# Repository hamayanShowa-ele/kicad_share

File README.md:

# kicad_share
kicad share data.

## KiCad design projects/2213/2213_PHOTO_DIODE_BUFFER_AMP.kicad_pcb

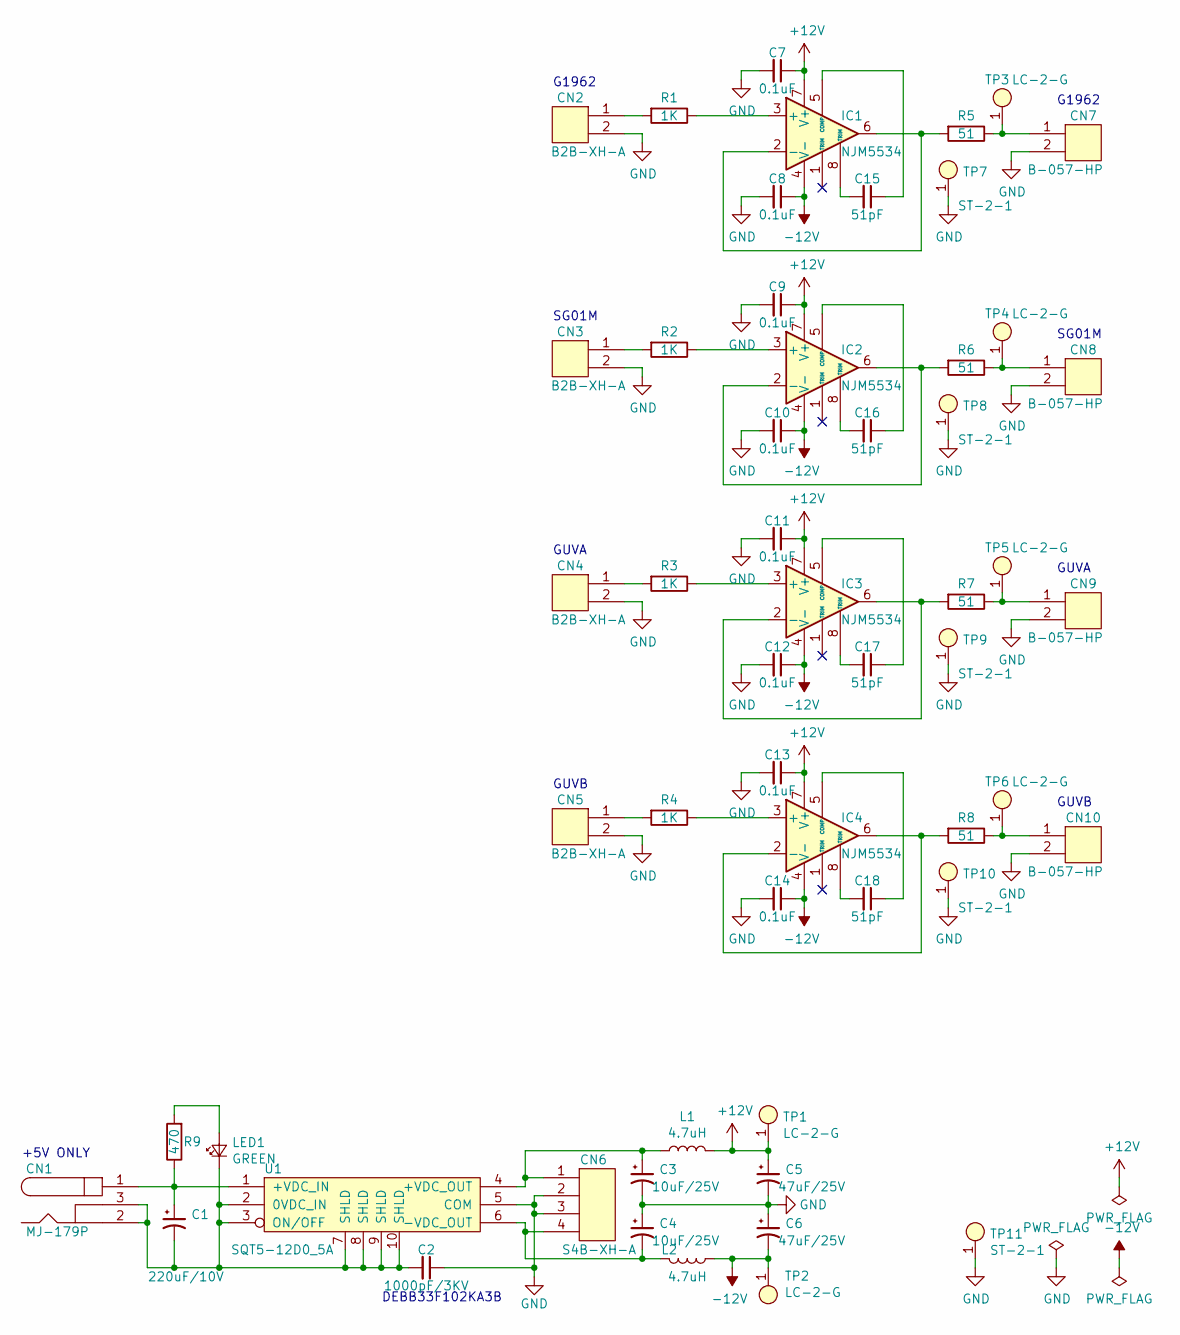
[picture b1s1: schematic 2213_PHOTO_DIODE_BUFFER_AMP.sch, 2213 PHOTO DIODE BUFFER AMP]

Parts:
C1: 220uF/10V; CP_Radial_D8.00mm_P2.50mm
C2: 1000pF/3KV; C_DEBB33F102KA
C3, C4: 10uF/25V; CP_D6R3_P2R5
C5, C6: 47uF/25V; CP_D6R3_P2R5
C7, C8, C9, C10, C11, C12, C13, C14: 0.1uF; C_TH_5R08
C15, C16, C17, C18: 51pF; C_TH_5R08
CN1: MJ-179P; cn_MJ-179P
CN2, CN3, CN4, CN5: B2B-XH-A; cn_B2B-XH-A
CN6: S4B-XH-A; cn_S4B-XH-A
CN7, CN8, CN9, CN10: B-057-HP; cn_BNC_B-057-HP
IC1, IC2, IC3, IC4: NJM5534; ic_DIP-8_W7.62mm
L1, L2: 4.7uH; l_LAL04SK4R7K
LED1: GREEN; LED_D3.0mm_center
R1, R2, R3, R4: 1K; R_TH_5R08
R5, R6, R7, R8: 51; R_TH_5R08
R9: 470; R_TH_5R08
TP1, TP2, TP3, TP4, TP5, TP6: LC-2-G; tp_LC-2-G
TP7, TP8, TP9, TP10, TP11: ST-2-1; tp_LC-2-G
U1: SQT5-12D0_5A; u_SQT5-24S05

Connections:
+12V: C5.1, C7.1, C9.1, C11.1, C13.1, IC1.7 (V+), IC2.7 (V+), IC3.7 (V+), IC4.7 (V+), L1.2, TP1.1
-12V: C6.2, C8.1, C10.1, C12.1, C14.1, IC1.4 (V-), IC2.4 (V-), IC3.4 (V-), IC4.4 (V-), L2.1, TP2.1
GND: C2.1, C3.2, C4.1, C5.2, C6.1, C7.2, C8.2, C9.2, C10.2, C11.2, C12.2, C13.2, C14.2, CN2.2, CN3.2, CN4.2, CN5.2, CN6.2, CN6.3, CN7.2, CN8.2, CN9.2, CN10.2, TP7.1, TP8.1, TP9.1, TP10.1, TP11.1, U1.5 (COM)
unnamed: C1.1, CN1.1, R9.1, U1.1 (+VDC_IN)
unnamed: C1.2, C2.2, CN1.2, CN1.3, LED1.2 (K), U1.2 (0VDC_IN), U1.3 (ON/OFF), U1.7 (SHLD), U1.8 (SHLD), U1.9 (SHLD), U1.10 (SHLD)
unnamed: C3.1, CN6.1, L1.1, U1.4 (+VDC_OUT)
unnamed: C4.2, CN6.4, L2.2, U1.6 (-VDC_OUT)
unnamed: C15.1, IC1.5 (COMP)
unnamed: C15.2, IC1.8 (TRIM)
unnamed: C16.1, IC2.5 (COMP)
unnamed: C16.2, IC2.8 (TRIM)
unnamed: C17.1, IC3.5 (COMP)
unnamed: C17.2, IC3.8 (TRIM)
unnamed: C18.1, IC4.5 (COMP)
unnamed: C18.2, IC4.8 (TRIM)
unnamed: CN2.1, R1.2
unnamed: CN3.1, R2.2
unnamed: CN4.1, R3.2
unnamed: CN5.1, R4.2
unnamed: CN7.1, R5.1, TP3.1
unnamed: CN8.1, R6.1, TP4.1
unnamed: CN9.1, R7.1, TP5.1
unnamed: CN10.1, R8.1, TP6.1
unnamed: IC1.2 (-), IC1.6, R5.2
unnamed: IC1.3 (+), R1.1
unnamed: IC2.2 (-), IC2.6, R6.2
unnamed: IC2.3 (+), R2.1
unnamed: IC3.2 (-), IC3.6, R7.2
unnamed: IC3.3 (+), R3.1
unnamed: IC4.2 (-), IC4.6, R8.2
unnamed: IC4.3 (+), R4.1
unnamed: LED1.1 (A), R9.2

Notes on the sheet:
+5V ONLY
G1962
SG01M
GUVA
GUVB
DEBB33F102KA3B

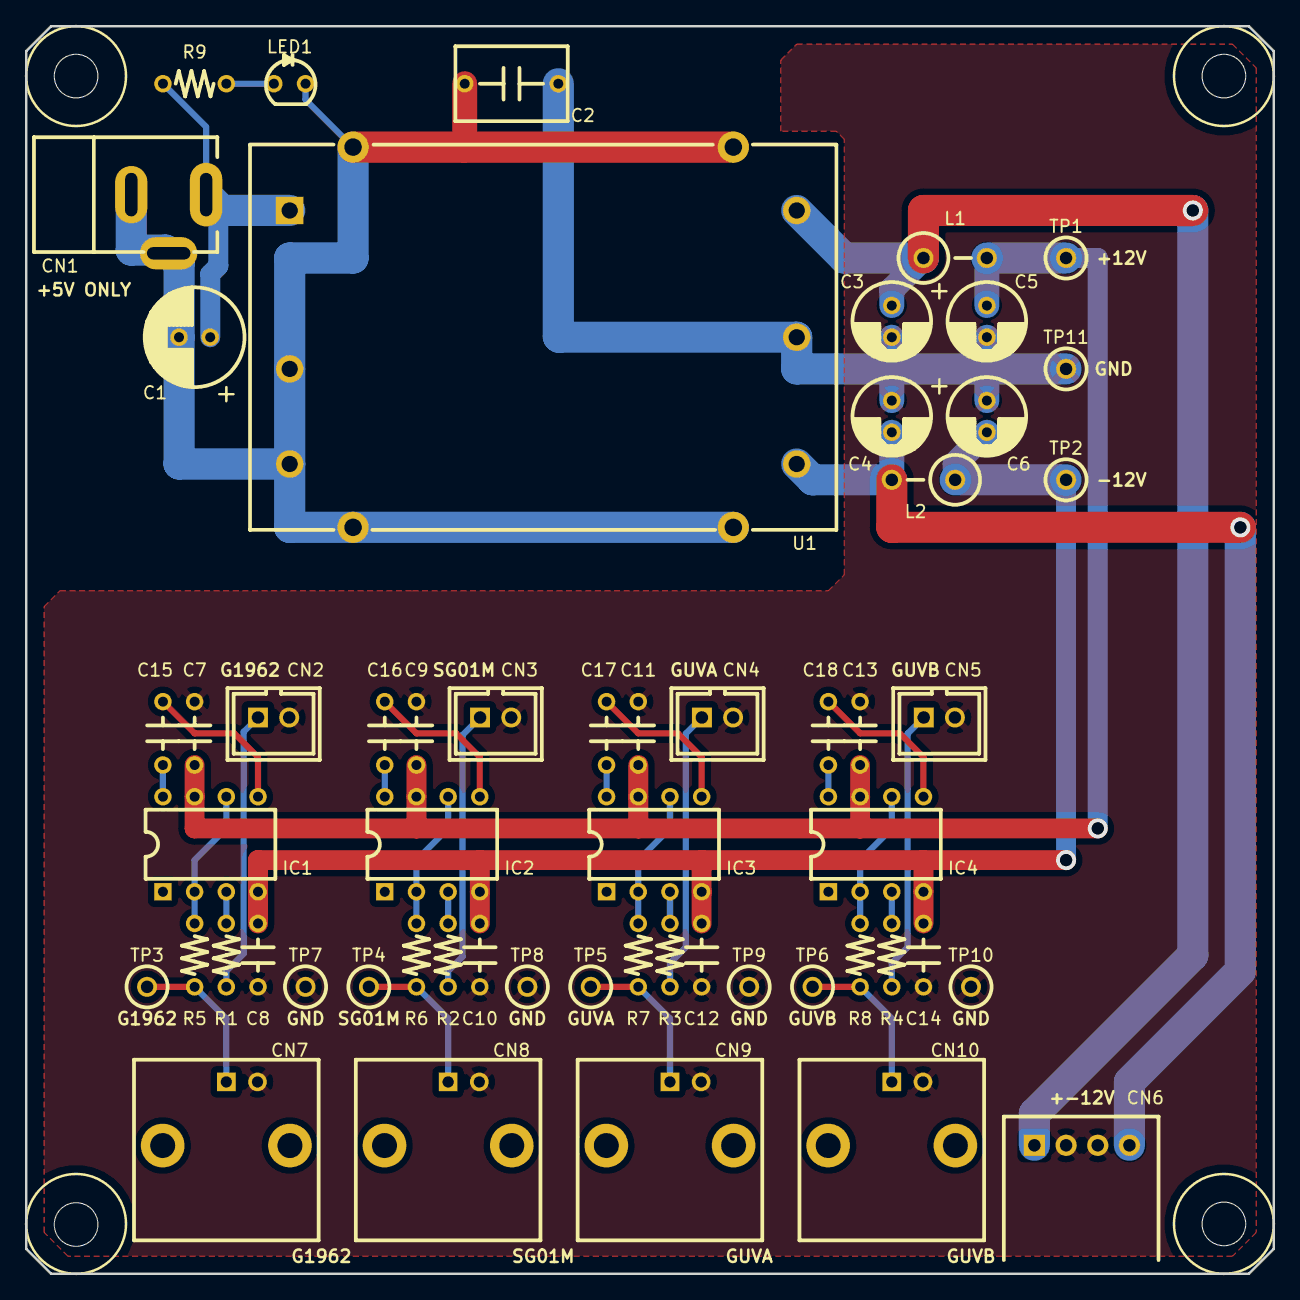
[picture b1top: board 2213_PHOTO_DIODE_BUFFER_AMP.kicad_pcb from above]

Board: 2 copper layers, 100.0 x 100.0 mm, 56 parts (0 on the bottom side), 32 nets.

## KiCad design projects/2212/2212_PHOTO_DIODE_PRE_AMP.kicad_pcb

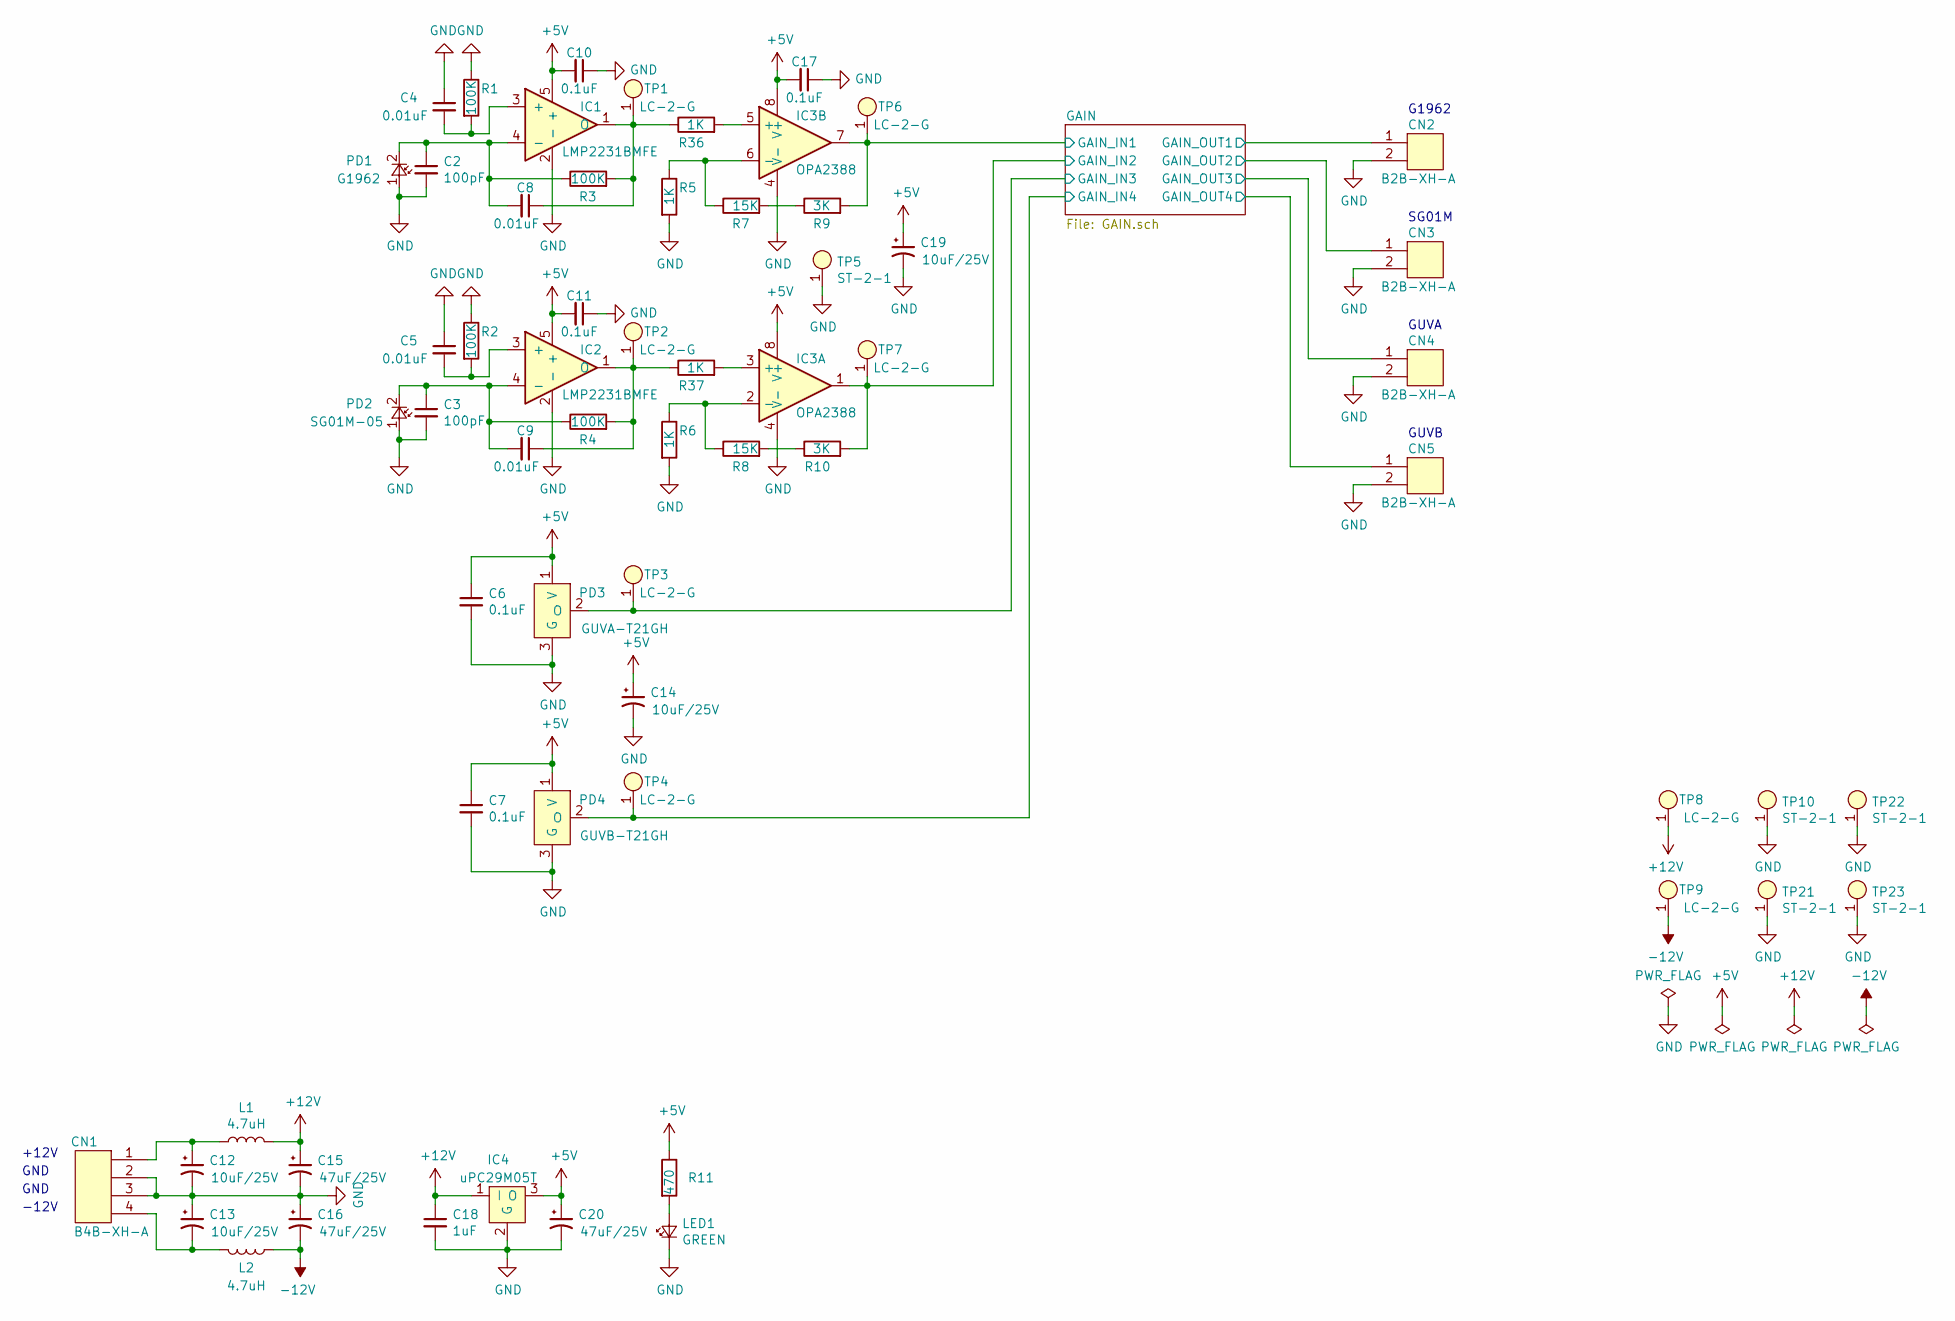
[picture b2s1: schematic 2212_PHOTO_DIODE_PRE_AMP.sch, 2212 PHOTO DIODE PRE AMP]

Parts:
C2, C3: 100pF; C_0603
C4, C5, C8, C9: 0.01uF; C_0603
C6, C7, C10, C11, C17: 0.1uF; C_0603
C12, C13, C14, C19: 10uF/25V; CP_Radial_D6.50mm_P2.50mm
C15, C16, C20: 47uF/25V; CP_Radial_D6.50mm_P2.50mm
C18: 1uF; C_0603
CN1: B4B-XH-A; cn_B4B-XH-A
CN2, CN3, CN4, CN5: B2B-XH-A; cn_B2B-XH-A
IC1, IC2: LMP2231BMFE; ic_SOT-23-5
IC3: OPA2388; SOIC-8
IC4: uPC29M05T; TO-252-2
L1, L2: 4.7uH; l_LAL04SK4R7K
LED1: GREEN; LED_D3.0mm_center
PD1: G1962; pd_G1962
PD2: SG01M-05; pd_SG01M
PD3: GUVA-T21GH; pd_GUVB-T21GH
PD4: GUVB-T21GH; pd_GUVB-T21GH
R1, R2, R3, R4: 100K; C_0805
R5, R6, R36, R37: 1K; C_0805
R7, R8: 15K; C_0805
R9, R10: 3K; C_0805
R11: 470; C_0603
TP1, TP2, TP3, TP4, TP6, TP7, TP8, TP9: LC-2-G; tp_LC-2-G
TP5, TP10, TP21, TP22, TP23: ST-2-1; tp_LC-2-G

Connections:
+5V: C6.1, C7.1, C10.2, C11.2, C14.1, C17.2, C19.1, C20.1, IC1.5 (+), IC2.5 (+), IC3.8 (V+), IC4.3 (O), PD3.1 (V), PD4.1 (V), R11.1
+12V: C15.1, C18.1, IC4.1 (I), L1.2, TP8.1; also elsewhere on the board
-12V: C16.2, L2.1, TP9.1; also elsewhere on the board
/GAIN/GAIN_IN1: IC3.7, R9.2, TP6.1; also elsewhere on the board
/GAIN/GAIN_IN2: IC3.1, R10.2, TP7.1; also elsewhere on the board
/GAIN/GAIN_IN3: PD3.2 (O), TP3.1; also elsewhere on the board
/GAIN/GAIN_IN4: PD4.2 (O), TP4.1; also elsewhere on the board
/GAIN/GAIN_OUT1: CN2.1; also elsewhere on the board
/GAIN/GAIN_OUT2: CN3.1; also elsewhere on the board
/GAIN/GAIN_OUT3: CN4.1; also elsewhere on the board
/GAIN/GAIN_OUT4: CN5.1; also elsewhere on the board
GND: C2.2, C3.2, C4.1, C5.1, C6.2, C7.2, C10.1, C11.1, C12.2, C13.1, C14.2, C15.2, C16.1, C17.1, C18.2, C19.2, C20.2, CN1.2, CN1.3, CN2.2, CN3.2, CN4.2, CN5.2, IC1.2 (-), IC2.2 (-), IC3.4 (V-), IC4.2 (G), LED1.2 (K), PD1.1, PD2.1, PD3.3 (G), PD4.3 (G), R1.1, R2.1, R5.2, R6.2, TP5.1, TP10.1, TP21.1, TP22.1, TP23.1; also elsewhere on the board
unnamed: C2.1, C8.2, IC1.4 (-), PD1.2, R3.1
unnamed: C3.1, C9.2, IC2.4 (-), PD2.2, R4.1
unnamed: C4.2, IC1.3 (+), R1.2
unnamed: C5.2, IC2.3 (+), R2.2
unnamed: C8.1, IC1.1 (O), R3.2, R36.1, TP1.1
unnamed: C9.1, IC2.1 (O), R4.2, R37.1, TP2.1
unnamed: C12.1, CN1.1, L1.1
unnamed: C13.2, CN1.4, L2.2
unnamed: IC3.2 (-), R6.1, R8.1
unnamed: IC3.3 (+), R37.2
unnamed: IC3.5 (+), R36.2
unnamed: IC3.6 (-), R5.1, R7.1
unnamed: LED1.1 (A), R11.2
unnamed: R7.2, R9.1
unnamed: R8.2, R10.1

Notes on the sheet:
+12V
G1962
SG01M
GUVA
GUVB
-12V
GND

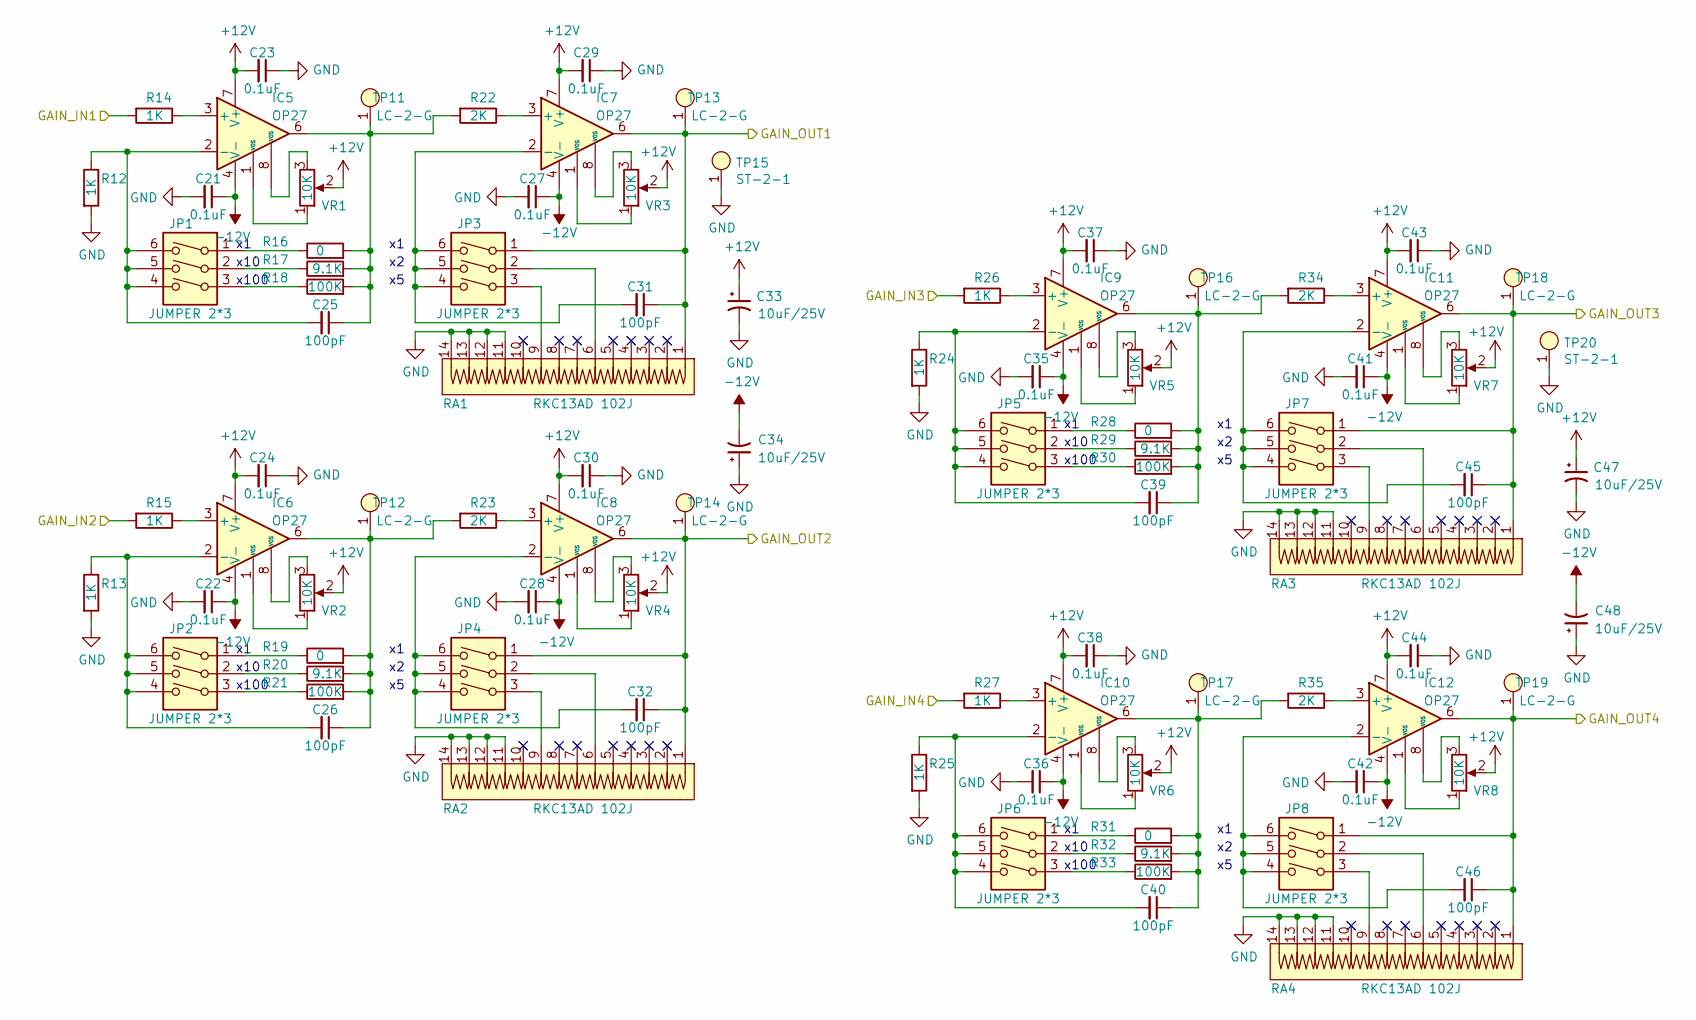
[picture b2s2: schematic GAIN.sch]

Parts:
C21, C22, C23, C24, C27, C28, C29, C30, C35, C36, C37, C38, C41, C42, C43, C44: 0.1uF; C_0603
C25, C26, C31, C32, C39, C40, C45, C46: 100pF; C_0603
C33, C34, C47, C48: 10uF/25V; CP_Radial_D6.50mm_P2.50mm
IC5, IC6, IC7, IC8, IC9, IC10, IC11, IC12: OP27; ic_DIP-8_W7.62mm
JP1, JP2, JP3, JP4, JP5, JP6, JP7, JP8: JUMPER 2*3; jp_JUMPER3x2
R12, R13, R14, R15, R24, R25, R26, R27: 1K; C_0805
R16, R19, R28, R31: 0; C_0805
R17, R20, R29, R32: 9.1K; C_0805
R18, R21, R30, R33: 100K; C_0805
R22, R23, R34, R35: 2K; C_0805
RA1, RA2, RA3, RA4: RKC13AD 102J; ra_RKC13AD
TP11, TP12, TP13, TP14, TP16, TP17, TP18, TP19: LC-2-G; tp_LC-2-G
TP15, TP20: ST-2-1; tp_LC-2-G
VR1, VR2, VR3, VR4, VR5, VR6, VR7, VR8: 10K; vr_TM-7EP

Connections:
+12V: C23.2, C24.2, C29.2, C30.2, C33.1, C37.2, C38.2, C43.2, C44.2, C47.1, IC5.7 (V+), IC6.7 (V+), IC7.7 (V+), IC8.7 (V+), IC9.7 (V+), IC10.7 (V+), IC11.7 (V+), IC12.7 (V+), VR1.2, VR2.2, VR3.2, VR4.2, VR5.2, VR6.2, VR7.2, VR8.2; also elsewhere on the board
-12V: C21.1, C22.1, C27.1, C28.1, C34.2, C35.1, C36.1, C41.1, C42.1, C48.2, IC5.4 (V-), IC6.4 (V-), IC7.4 (V-), IC8.4 (V-), IC9.4 (V-), IC10.4 (V-), IC11.4 (V-), IC12.4 (V-); also elsewhere on the board
/GAIN/GAIN_IN1: R14.2; also elsewhere on the board
/GAIN/GAIN_IN2: R15.2; also elsewhere on the board
/GAIN/GAIN_IN3: R26.2; also elsewhere on the board
/GAIN/GAIN_IN4: R27.2; also elsewhere on the board
/GAIN/GAIN_OUT1: C31.1, IC7.6, JP3.1, RA1.1, TP13.1; also elsewhere on the board
/GAIN/GAIN_OUT2: C32.1, IC8.6, JP4.1, RA2.1, TP14.1; also elsewhere on the board
/GAIN/GAIN_OUT3: C45.1, IC11.6, JP7.1, RA3.1, TP18.1; also elsewhere on the board
/GAIN/GAIN_OUT4: C46.1, IC12.6, JP8.1, RA4.1, TP19.1; also elsewhere on the board
GND: C21.2, C22.2, C23.1, C24.1, C27.2, C28.2, C29.1, C30.1, C33.2, C34.1, C35.2, C36.2, C37.1, C38.1, C41.2, C42.2, C43.1, C44.1, C47.2, C48.1, R12.2, R13.2, R24.2, R25.2, RA1.11, RA1.12, RA1.13, RA1.14, RA2.11, RA2.12, RA2.13, RA2.14, RA3.11, RA3.12, RA3.13, RA3.14, RA4.11, RA4.12, RA4.13, RA4.14, TP15.1, TP20.1; also elsewhere on the board
unnamed: C25.1, IC5.6, R16.2, R17.2, R18.2, R22.2, TP11.1
unnamed: C25.2, IC5.2 (-), JP1.4, JP1.5, JP1.6, R12.1
unnamed: C26.1, IC6.6, R19.2, R20.2, R21.2, R23.2, TP12.1
unnamed: C26.2, IC6.2 (-), JP2.4, JP2.5, JP2.6, R13.1
unnamed: C31.2, IC7.2 (-), JP3.4, JP3.5, JP3.6
unnamed: C32.2, IC8.2 (-), JP4.4, JP4.5, JP4.6
unnamed: C39.1, IC9.6, R28.2, R29.2, R30.2, R34.2, TP16.1
unnamed: C39.2, IC9.2 (-), JP5.4, JP5.5, JP5.6, R24.1
unnamed: C40.1, IC10.6, R31.2, R32.2, R33.2, R35.2, TP17.1
unnamed: C40.2, IC10.2 (-), JP6.4, JP6.5, JP6.6, R25.1
unnamed: C45.2, IC11.2 (-), JP7.4, JP7.5, JP7.6
unnamed: C46.2, IC12.2 (-), JP8.4, JP8.5, JP8.6
unnamed: IC5.1 (VOS), VR1.1
unnamed: IC5.3 (+), R14.1
unnamed: IC5.8 (VOS), VR1.3
unnamed: IC6.1 (VOS), VR2.1
unnamed: IC6.3 (+), R15.1
unnamed: IC6.8 (VOS), VR2.3
unnamed: IC7.1 (VOS), VR3.1
unnamed: IC7.3 (+), R22.1
unnamed: IC7.8 (VOS), VR3.3
unnamed: IC8.1 (VOS), VR4.1
unnamed: IC8.3 (+), R23.1
unnamed: IC8.8 (VOS), VR4.3
unnamed: IC9.1 (VOS), VR5.1
unnamed: IC9.3 (+), R26.1
unnamed: IC9.8 (VOS), VR5.3
unnamed: IC10.1 (VOS), VR6.1
unnamed: IC10.3 (+), R27.1
unnamed: IC10.8 (VOS), VR6.3
unnamed: IC11.1 (VOS), VR7.1
unnamed: IC11.3 (+), R34.1
unnamed: IC11.8 (VOS), VR7.3
unnamed: IC12.1 (VOS), VR8.1
unnamed: IC12.3 (+), R35.1
unnamed: IC12.8 (VOS), VR8.3
unnamed: JP1.1, R16.1
unnamed: JP1.2, R17.1
unnamed: JP1.3, R18.1
unnamed: JP2.1, R19.1
unnamed: JP2.2, R20.1
unnamed: JP2.3, R21.1
unnamed: JP3.2, RA1.6
unnamed: JP3.3, RA1.9
unnamed: JP4.2, RA2.6
unnamed: JP4.3, RA2.9
unnamed: JP5.1, R28.1
unnamed: JP5.2, R29.1
unnamed: JP5.3, R30.1
unnamed: JP6.1, R31.1
unnamed: JP6.2, R32.1
unnamed: JP6.3, R33.1
unnamed: JP7.2, RA3.6
unnamed: JP7.3, RA3.9
unnamed: JP8.2, RA4.6
unnamed: JP8.3, RA4.9

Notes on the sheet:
x10
x100

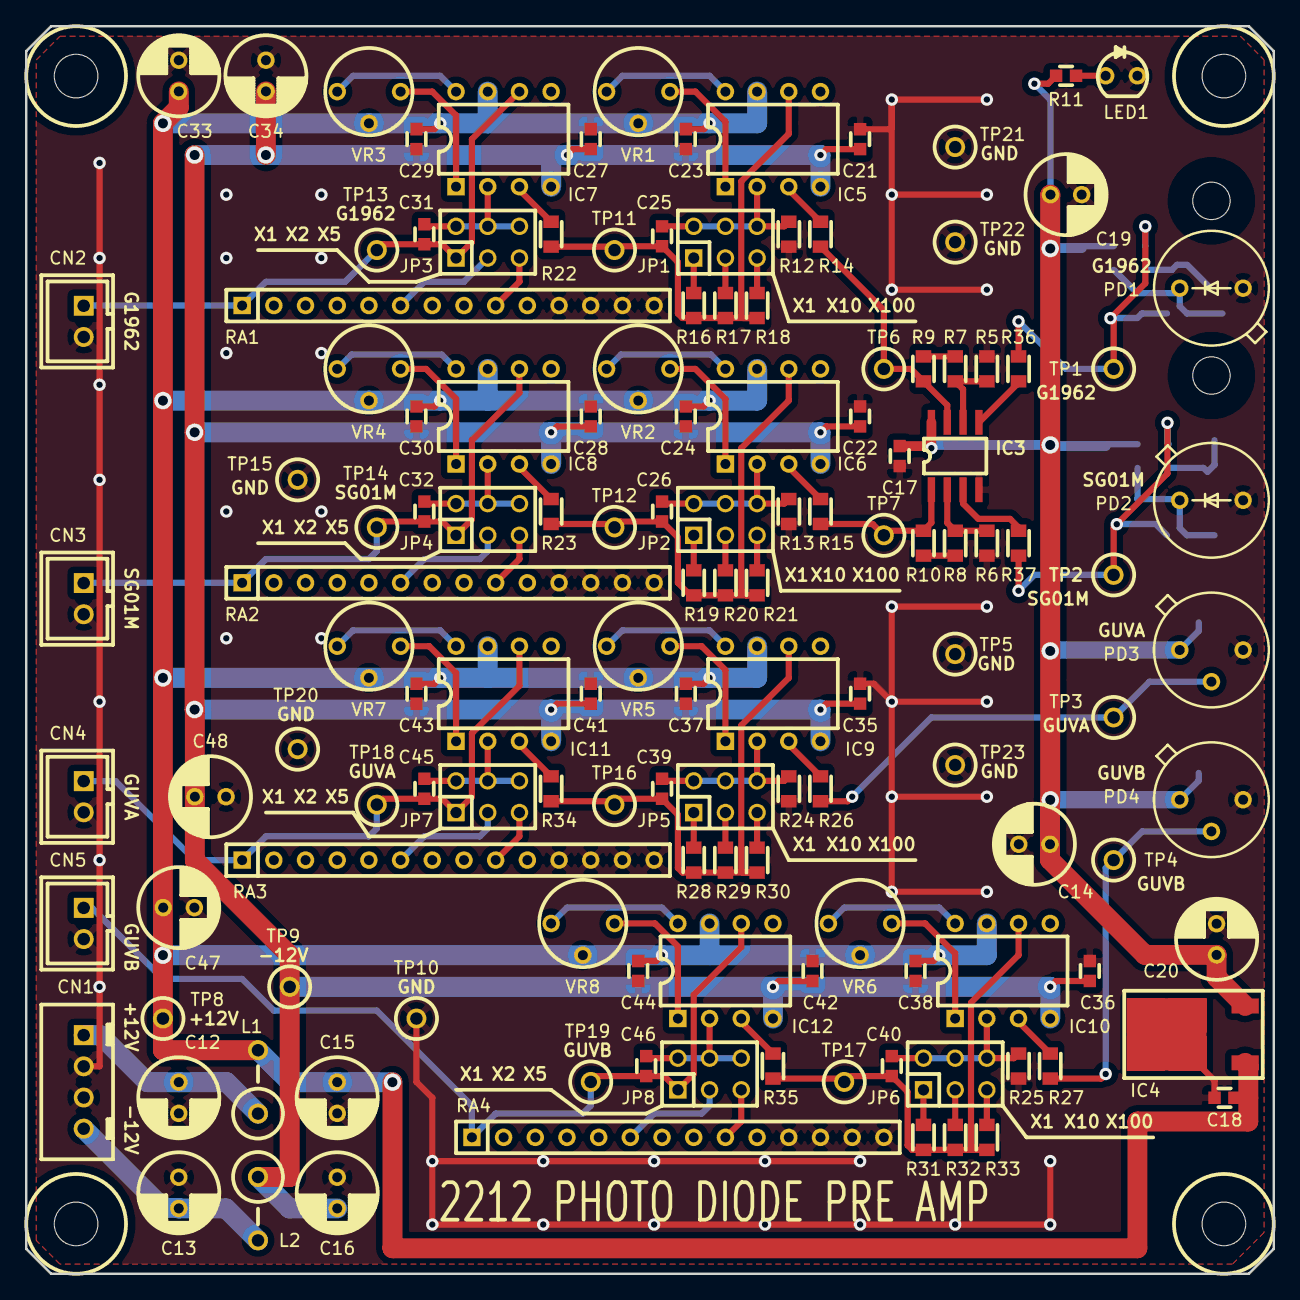
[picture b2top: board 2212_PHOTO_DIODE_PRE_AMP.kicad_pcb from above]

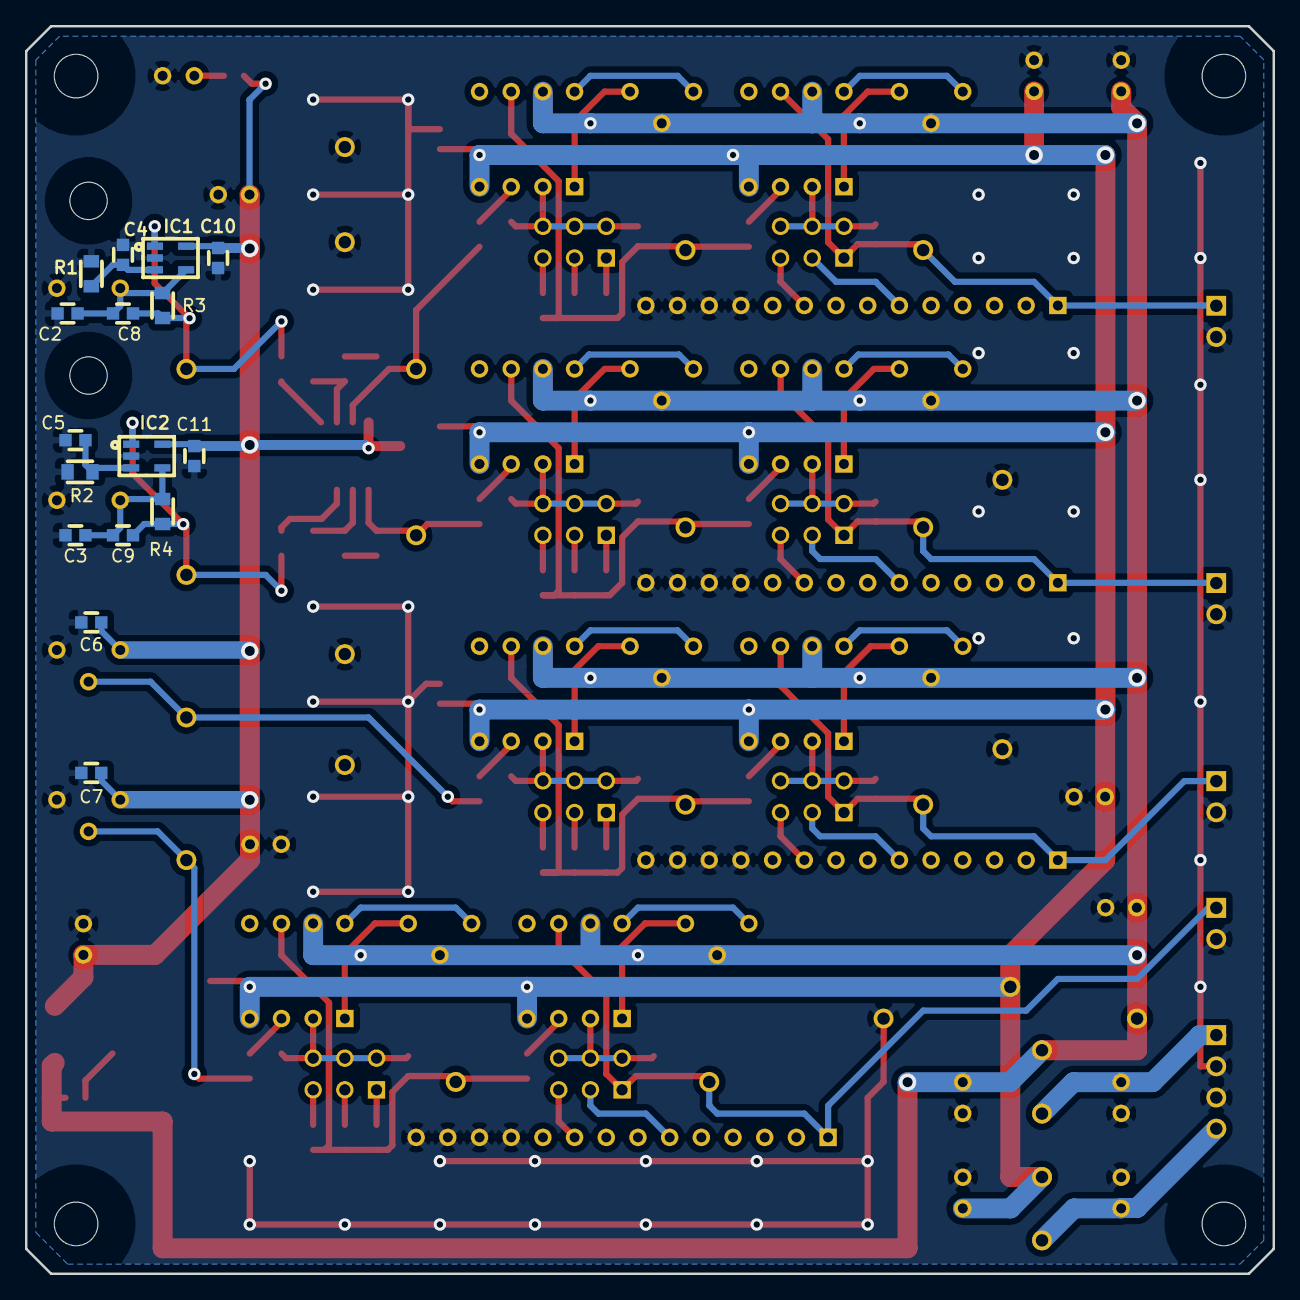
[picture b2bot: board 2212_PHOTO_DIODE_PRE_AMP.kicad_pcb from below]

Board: 2 copper layers, 100.0 x 100.0 mm, 151 parts (16 on the bottom side), 83 nets.

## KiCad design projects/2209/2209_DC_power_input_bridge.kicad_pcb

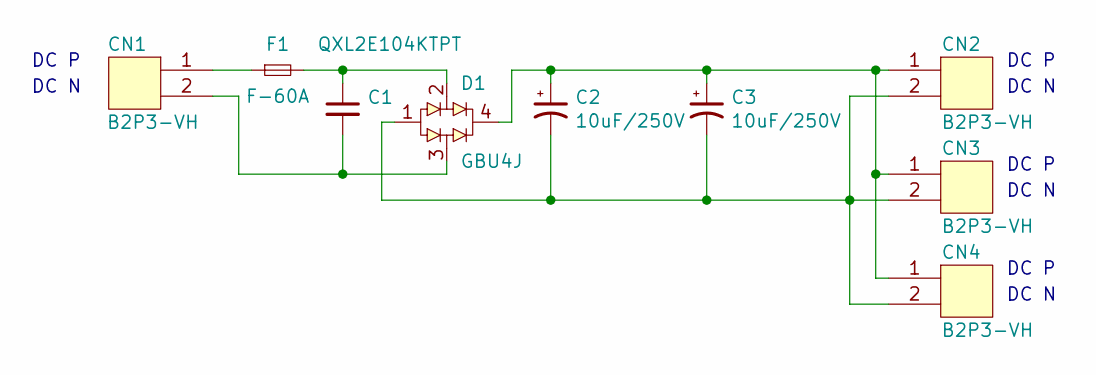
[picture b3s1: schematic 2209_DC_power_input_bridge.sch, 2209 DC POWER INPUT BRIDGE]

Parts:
C1: QXL2E104KTPT; C_TH_15R24
C2, C3: 10uF/250V; CP_Radial_D10.0mm_P5.00mm
CN1, CN2, CN3, CN4: B2P3-VH; cn_B2P3-VH
D1: GBU4J; d_GBU4J
F1: F-60A; f_F-60-A

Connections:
unnamed: C1.1, D1.2, F1.2
unnamed: C1.2, CN1.2, D1.3
unnamed: C2.1, C3.1, CN2.1, CN3.1, CN4.1, D1.4
unnamed: C2.2, C3.2, CN2.2, CN3.2, CN4.2, D1.1
unnamed: CN1.1, F1.1

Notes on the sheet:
DC P
DC N

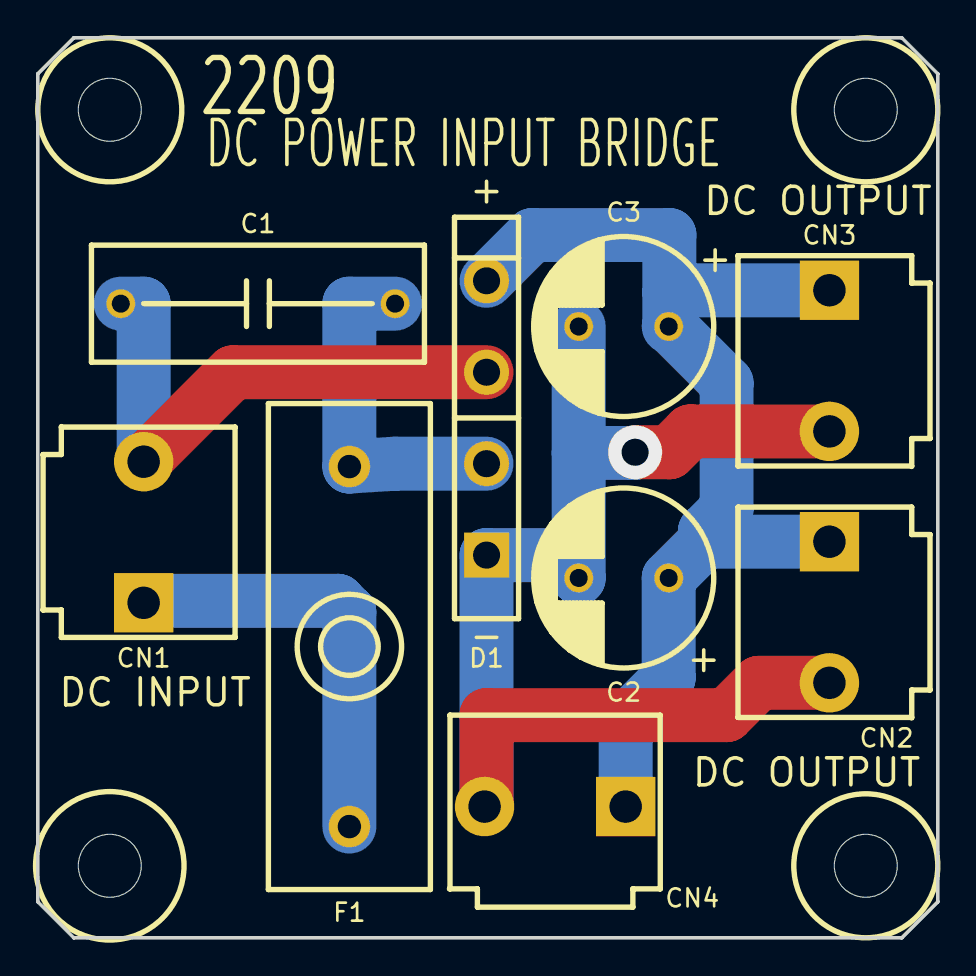
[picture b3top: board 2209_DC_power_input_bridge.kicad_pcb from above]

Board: 2 copper layers, 50.0 x 50.0 mm, 9 parts (0 on the bottom side), 5 nets.

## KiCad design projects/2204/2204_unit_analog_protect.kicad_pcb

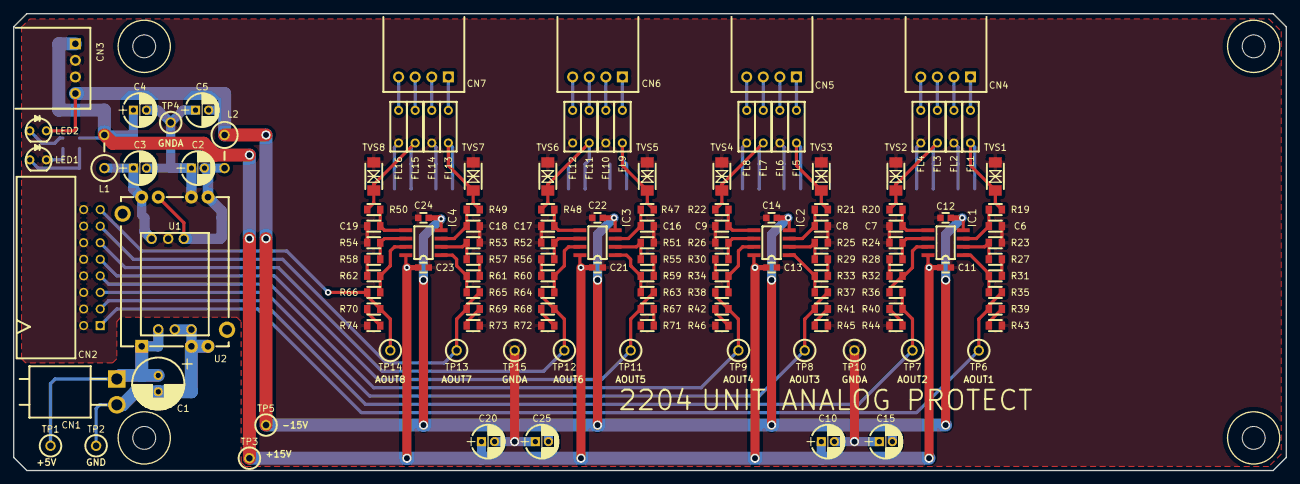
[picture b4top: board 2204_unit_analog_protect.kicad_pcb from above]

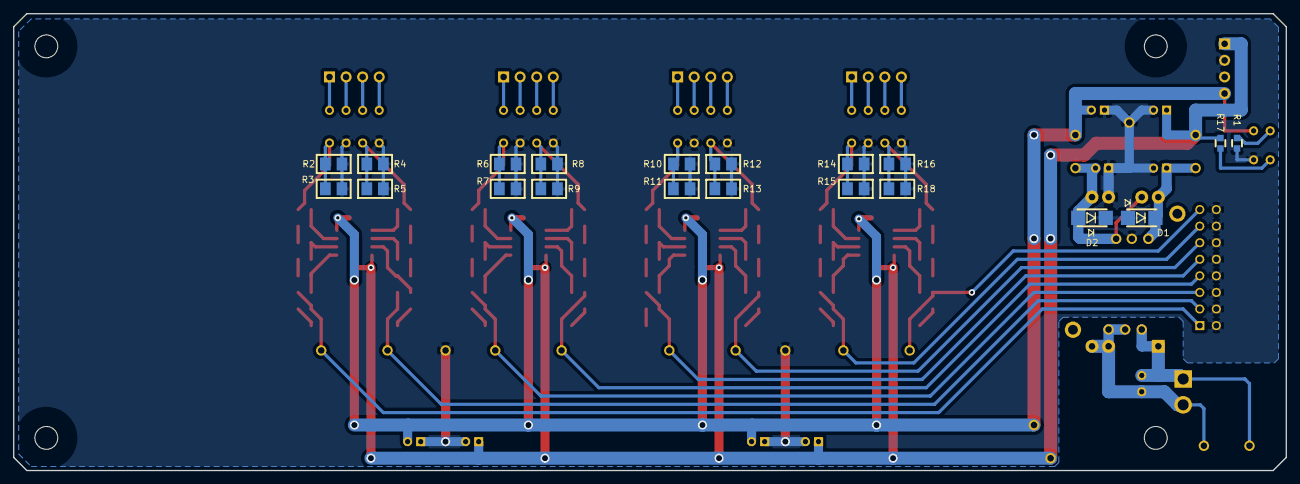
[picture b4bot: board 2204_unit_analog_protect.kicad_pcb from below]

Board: 2 copper layers, 195.0 x 70.0 mm, 157 parts (20 on the bottom side), 81 nets.

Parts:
C1: 220uF/10V; CP_Radial_D8.00mm_P2.50mm
C2, C3: 22uF/50V; CP_Radial_D5.0mm_P2.00mm
C4, C5: 10uF/50V; CP_Radial_D5.0mm_P2.00mm
C6, C7, C8, C9, C16, C17, C18, C19: 1000pF; C_0805
C10, C15, C20, C25: 10uF/35V; CP_Radial_D5.0mm_P2.00mm
C11, C12, C13, C14, C21, C22, C23, C24: 0.1uF; C_0603
CN1: B2PS-VH; cn_B2PS-VH
CN2: HIF3FC-16PA-2.54DS; cn_HIF3FC-16PA-254DS
CN3, CN4, CN5, CN6, CN7: S4B-XH-A; cn_S4B-XH-A
D1, D2: RB160L-40; d_RB160L-40
FL1, FL2, FL3, FL4, FL5, FL6, FL7, FL8, FL9, FL10, FL11, FL12, FL13, FL14, FL15, FL16: ZBF503D-00(TA)-01; fl_ZBF503D-00
IC1, IC2, IC3, IC4: OP2177ARZ; SOIC-8
L1, L2: LAL04SK4R7K; l_LAL04SK4R7K
LED1: GREEN; LED_D3.0mm_center
LED2: ORANGE; LED_D3.0mm_center
R1, R17: 2.7K; C_0603
R2, R3, R4, R5, R6, R7, R8, R9, R10, R11, R12, R13, R14, R15, R16, R18: 100; C_3216
R19, R20, R21, R22, R47, R48, R49, R50: 1.6K; C_0805
R23, R24, R25, R26, R51, R52, R53, R54: N.M.; C_0805
R27, R28, R29, R30, R31, R32, R33, R34, R43, R44, R45, R46, R55, R56, R57, R58, R59, R60, R61, R62, R71, R72, R73, R74: 0; C_0805
R35, R36, R37, R38, R63, R64, R65, R66: 2K; C_0805
R39, R40, R41, R42, R67, R68, R69, R70: 1.5K; C_0805
TP1, TP3, TP5, TP6, TP7, TP8, TP9, TP11, TP12, TP13, TP14: LC-2-G; tp_LC-2-G
TP2, TP4, TP10, TP15: ST-2-1; tp_LC-2-G
TVS1, TVS2, TVS3, TVS4, TVS5, TVS6, TVS7, TVS8: ZS1018; d_ZS1018
U1: CCG3-12-15DF; u_CCG3-12-15DF
U2: CC3-0512DF-E; u_CC3-0512SF-E

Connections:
+5V: C1.1, CN1.1, TP1.1, U1.1, U2.1
+15V: C4.1, C10.1, C11.1, C13.1, C20.1, C21.1, C23.1, CN3.1, IC1.8, IC2.8, IC3.8, IC4.8, L1.2, R17.1, TP3.1
-15V: C5.2, C12.1, C14.1, C15.2, C22.1, C24.1, C25.2, CN3.4, IC1.4, IC2.4, IC3.4, IC4.4, L2.1, LED2.2, TP5.1
/AIN1: FL1.1, R2.2, R3.2, R19.2, TVS1.1
/AIN2: FL3.1, R4.2, R5.2, R20.2, TVS2.1
/AIN3: FL5.1, R6.2, R7.2, R21.2, TVS3.1
/AIN4: FL7.1, R8.2, R9.2, R22.2, TVS4.1
/AIN5: FL9.1, R10.2, R11.2, R47.2, TVS5.1
/AIN6: FL11.1, R12.2, R13.2, R48.2, TVS6.1
/AIN7: FL13.1, R14.2, R15.2, R49.2, TVS7.1
/AIN8: FL15.1, R16.2, R18.2, R50.2, TVS8.1
/AOUT1: CN2.1, R35.1, R39.1, TP6.1
/AOUT2: CN2.3, R36.1, R40.1, TP7.1
/AOUT3: CN2.5, R37.1, R41.1, TP8.1
/AOUT4: CN2.7, R38.1, R42.1, TP9.1
/AOUT5: CN2.9, R63.1, R67.1, TP11.1
/AOUT6: CN2.11, R64.1, R68.1, TP12.1
/AOUT7: CN2.13, R65.1, R69.1, TP13.1
/AOUT8: CN2.15, R66.1, R70.1, TP14.1
GND: C1.2, CN1.2, TP2.1, U1.2, U1.3, U2.2, U2.3
GNDA: C2.1, C3.2, C4.2, C5.1, C6.2, C7.2, C8.2, C9.2, C10.2, C11.2, C12.2, C13.2, C14.2, C15.1, C16.2, C17.2, C18.2, C19.2, C20.2, C21.2, C22.2, C23.2, C24.2, C25.1, CN2.2, CN2.4, CN2.6, CN2.8, CN2.10, CN2.12, CN2.14, CN2.16, CN3.2, CN3.3, D1.1, D2.2, FL2.1, FL4.1, FL6.1, FL8.1, FL10.1, FL12.1, FL14.1, FL16.1, LED1.2, R1.2, R2.1, R3.1, R4.1, R5.1, R6.1, R7.1, R8.1, R9.1, R10.1, R11.1, R12.1, R13.1, R14.1, R15.1, R16.1, R18.1, R23.2, R24.2, R25.2, R26.2, R43.2, R44.2, R45.2, R46.2, R51.2, R52.2, R53.2, R54.2, R71.2, R72.2, R73.2, R74.2, TP4.1, TP10.1, TP15.1, TVS1.2, TVS2.2, TVS3.2, TVS4.2, TVS5.2, TVS6.2, TVS7.2, TVS8.2, U1.5, U2.5
unnamed: C2.2, D2.1, L2.2, U1.4, U2.4, U2.6
unnamed: C3.1, D1.2, L1.1, U1.6, U2.7
unnamed: C6.1, IC1.3, R19.1
unnamed: C7.1, IC1.5, R20.1
unnamed: C8.1, IC2.3, R21.1
unnamed: C9.1, IC2.5, R22.1
unnamed: C16.1, IC3.3, R47.1
unnamed: C17.1, IC3.5, R48.1
unnamed: C18.1, IC4.3, R49.1
unnamed: C19.1, IC4.5, R50.1
unnamed: CN4.1, FL1.2
unnamed: CN4.2, FL2.2
unnamed: CN4.3, FL3.2
unnamed: CN4.4, FL4.2
unnamed: CN5.1, FL5.2
unnamed: CN5.2, FL6.2
unnamed: CN5.3, FL7.2
unnamed: CN5.4, FL8.2
unnamed: CN6.1, FL9.2
unnamed: CN6.2, FL10.2
unnamed: CN6.3, FL11.2
unnamed: CN6.4, FL12.2
unnamed: CN7.1, FL13.2
unnamed: CN7.2, FL14.2
unnamed: CN7.3, FL15.2
unnamed: CN7.4, FL16.2
unnamed: IC1.1, R31.1, R35.2
unnamed: IC1.2, R23.1, R27.2
unnamed: IC1.6, R24.1, R28.2
unnamed: IC1.7, R32.1, R36.2
unnamed: IC2.1, R33.1, R37.2
unnamed: IC2.2, R25.1, R29.2
unnamed: IC2.6, R26.1, R30.2
unnamed: IC2.7, R34.1, R38.2
unnamed: IC3.1, R59.1, R63.2
unnamed: IC3.2, R51.1, R55.2
unnamed: IC3.6, R52.1, R56.2
unnamed: IC3.7, R60.1, R64.2
unnamed: IC4.1, R61.1, R65.2
unnamed: IC4.2, R53.1, R57.2
unnamed: IC4.6, R54.1, R58.2
unnamed: IC4.7, R62.1, R66.2
unnamed: LED1.1, R17.2
unnamed: LED2.1, R1.1
unnamed: R27.1, R31.2
unnamed: R28.1, R32.2
unnamed: R29.1, R33.2
unnamed: R30.1, R34.2
unnamed: R39.2, R43.1
unnamed: R40.2, R44.1
unnamed: R41.2, R45.1
unnamed: R42.2, R46.1
unnamed: R55.1, R59.2
unnamed: R56.1, R60.2
unnamed: R57.1, R61.2
unnamed: R58.1, R62.2
unnamed: R67.2, R71.1
unnamed: R68.2, R72.1
unnamed: R69.2, R73.1
unnamed: R70.2, R74.1
